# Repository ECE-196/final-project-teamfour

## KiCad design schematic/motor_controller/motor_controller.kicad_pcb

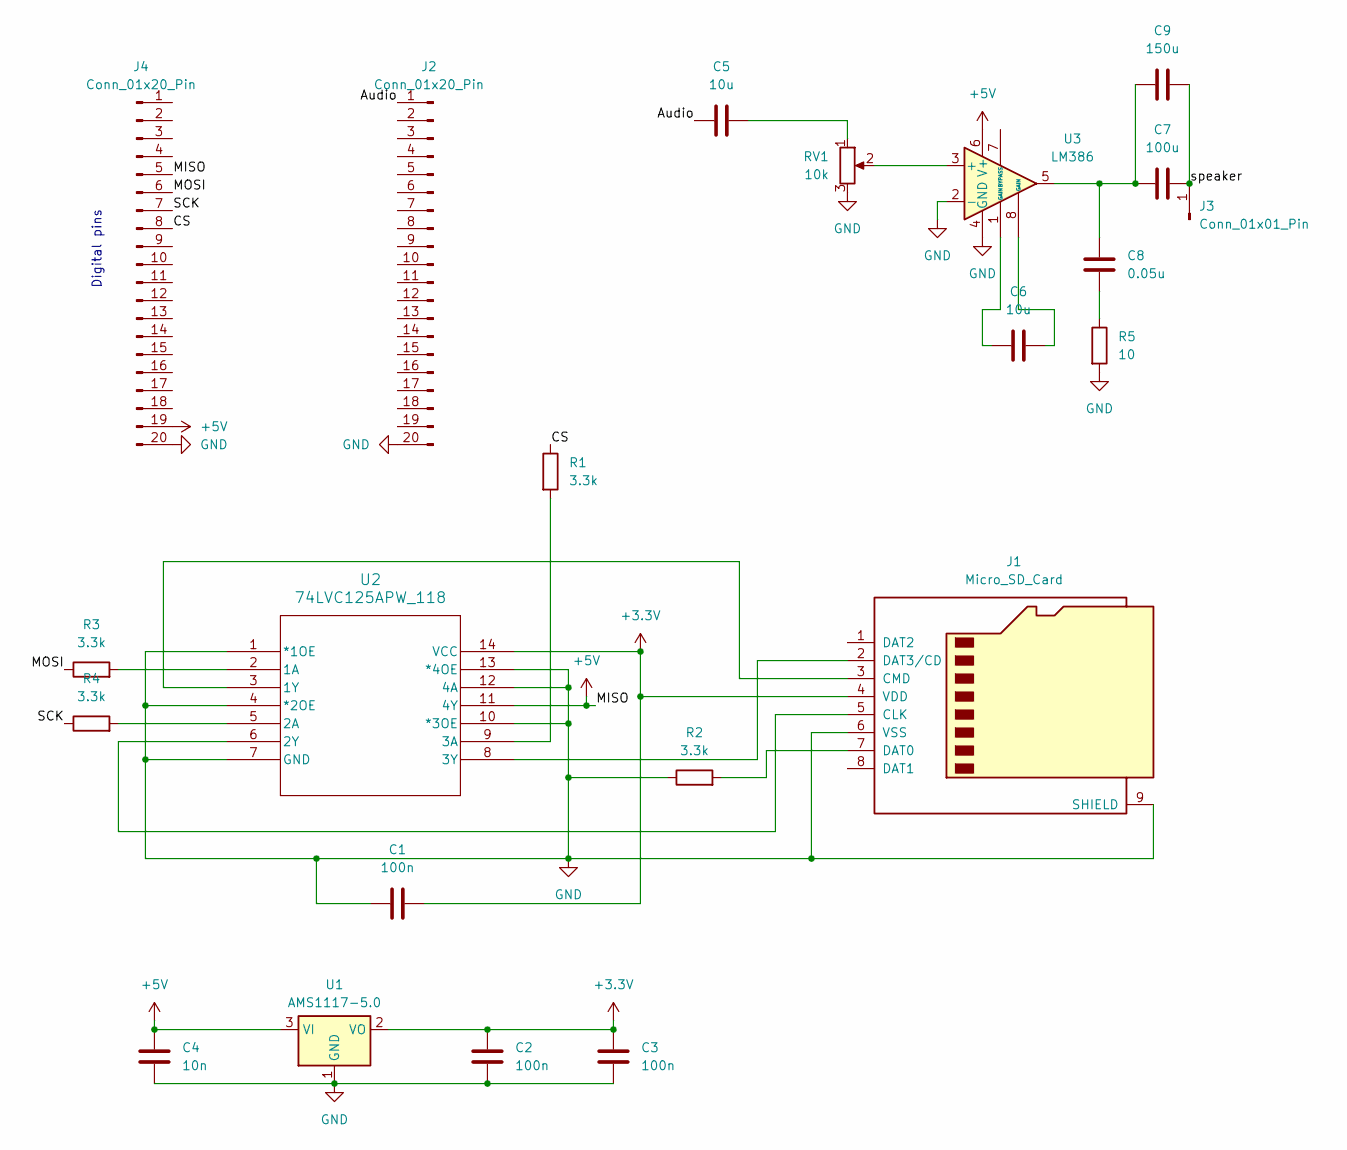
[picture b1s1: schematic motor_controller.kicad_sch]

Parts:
C1, C2, C3: 100n; C_0402_1005Metric
C4: 10n; C_0402_1005Metric
C5, C6: 10u; C_1210_3225Metric
C7: 100u; C_Elec_6.3x5.8
C8: 0.05u; C_1206_3216Metric
C9: 150u; C_Elec_6.3x7.7
J1: Micro_SD_Card; microSD_HC_Molex_104031-0811
J2, J4: Conn_01x20_Pin; PinHeader_1x20_P2.54mm_Vertical
J3: Conn_01x01_Pin; PinHeader_1x01_P1.00mm_Vertical
R1, R2, R3, R4: 3.3k; R_0402_1005Metric
R5: 10; R_0402_1005Metric
RV1: 10k; Potentiometer_Alpha_RD901F-40-00D_Single_Vertical
U1: AMS1117-5.0; SOT229P700X180-4N
U2: 74LVC125APW_118; IC_74LVC125APW_118
U3: LM386; DIP-8_W7.62mm

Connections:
+3.3V: C1.2, C2.1, C3.1, J1.4 (VDD), U1.2 (VO), U2.14 (VCC)
+5V: C4.1, J4.5, J4.19, U1.3 (VI), U2.11 (4Y), U3.6 (V+)
/Audio: C5.1, J2.1
/CS: J4.8, R1.1
/MOSI: J4.6, R3.1
/SCK: J4.7, R4.1
/speaker: C7.2, C9.2, J3.1
GND: C1.1, C2.2, C3.2, C4.2, J1.6 (VSS), J1.9 (SHIELD), J2.20, J4.20, R2.1, R5.2, RV1.3, U1.1 (GND), U2.1 (*1OE), U2.4 (*2OE), U2.7 (GND), U2.10 (*3OE), U2.12 (4A), U2.13 (*4OE), U3.2 (-), U3.4 (GND)
unnamed: C5.2, RV1.1
unnamed: C6.1, U3.1 (GAIN)
unnamed: C6.2, U3.8 (GAIN)
unnamed: C7.1, C8.2, C9.1, U3.5
unnamed: C8.1, R5.1
unnamed: J1.5 (CLK), U2.6 (2Y)
unnamed: J1.3 (CMD), U2.3 (1Y)
unnamed: J1.7 (DAT0), R2.2
unnamed: J1.2 (DAT3/CD), U2.8 (3Y)
unnamed: R3.2, U2.2 (1A)
unnamed: R4.2, U2.5 (2A)
unnamed: R1.2, U2.9 (3A)
unnamed: RV1.2, U3.3 (+)

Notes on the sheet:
Digital pins

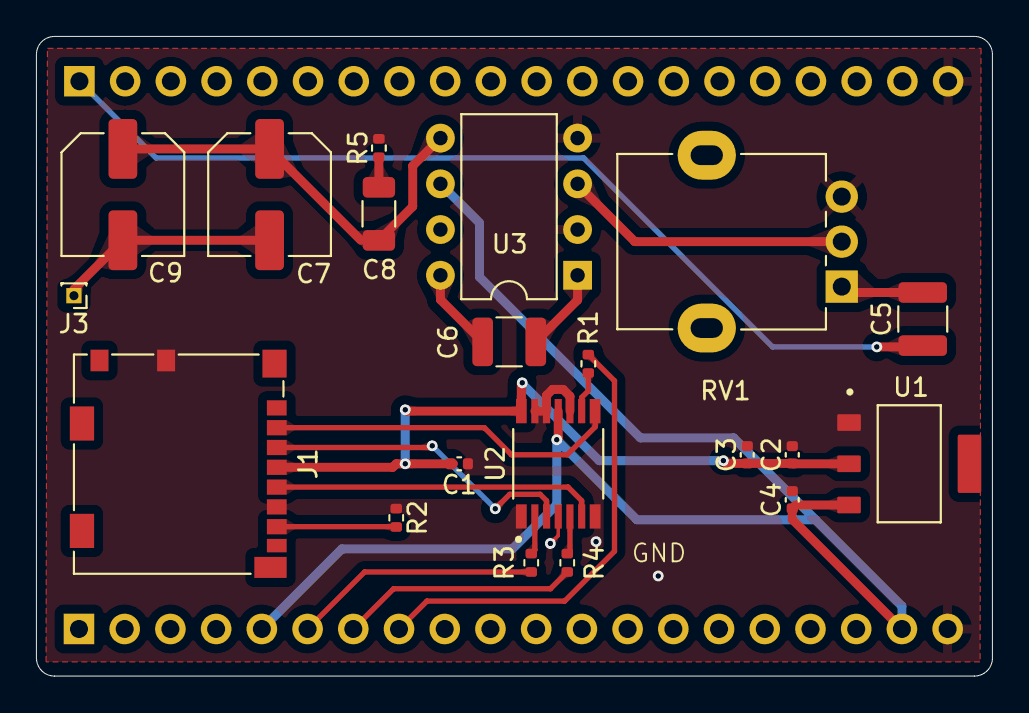
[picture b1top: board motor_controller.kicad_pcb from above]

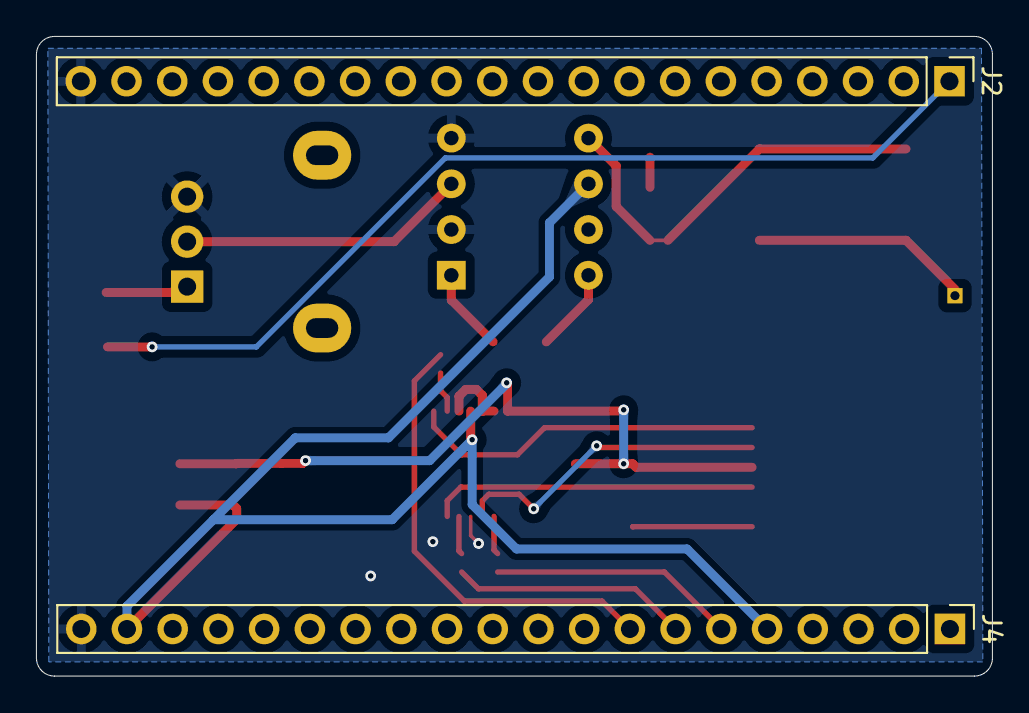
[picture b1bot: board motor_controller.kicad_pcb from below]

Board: 2 copper layers, 53.1 x 35.5 mm, 22 parts (2 on the bottom side), 21 nets.

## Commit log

2024-10-28 pcb schematic
2024-10-31 Final schematic for review
2024-10-31 Final schematic reviewed
2024-11-03 First_Code_for_OLED
2024-11-03 FIrst_OLED_Code
2024-11-07 add CAD files for dispensing mechanism and enclosure
2024-11-11 Initial servo code
    code to initialize and drive the 4 servos
2024-11-11 Gear CAD with axle
    updated CAD for the gears now including the axle and fixation for screw
2024-11-11 Initial sensor code
    initial sensor code that prints data in Arduino serial window
2024-11-19 Uploading_initial_AppCode
2024-11-19 Added_ArduinoforESP32
2024-11-20 final version for enclosure vector files
2024-11-20 Updated_app_code_WithTime
2024-11-24 App_with_motor_config
2024-11-25 Added_userDets_screen
2024-11-26 Adding_the_servo+bluetooth_Combined_code
2024-11-27 EditedTo_DIspense_Based_On_DosageAndTIme
2024-11-27 Access_PillDetails_AcrossWholeApp
2024-11-30 Improved_UI
2024-11-30 audio code for speaker
2024-12-01 allow screent to display the sensor measurements
2024-12-01 updated_BLE_Advertising
2024-12-01 Updated_App_with_humidity
2024-12-01 Added_OLEDandServoToBluetoothCode
2024-12-03 Added_speaker_to_OLED_BLE_APP_code
2024-12-03 updated_beep_function
2024-12-04 hopefully_last_fix_up
